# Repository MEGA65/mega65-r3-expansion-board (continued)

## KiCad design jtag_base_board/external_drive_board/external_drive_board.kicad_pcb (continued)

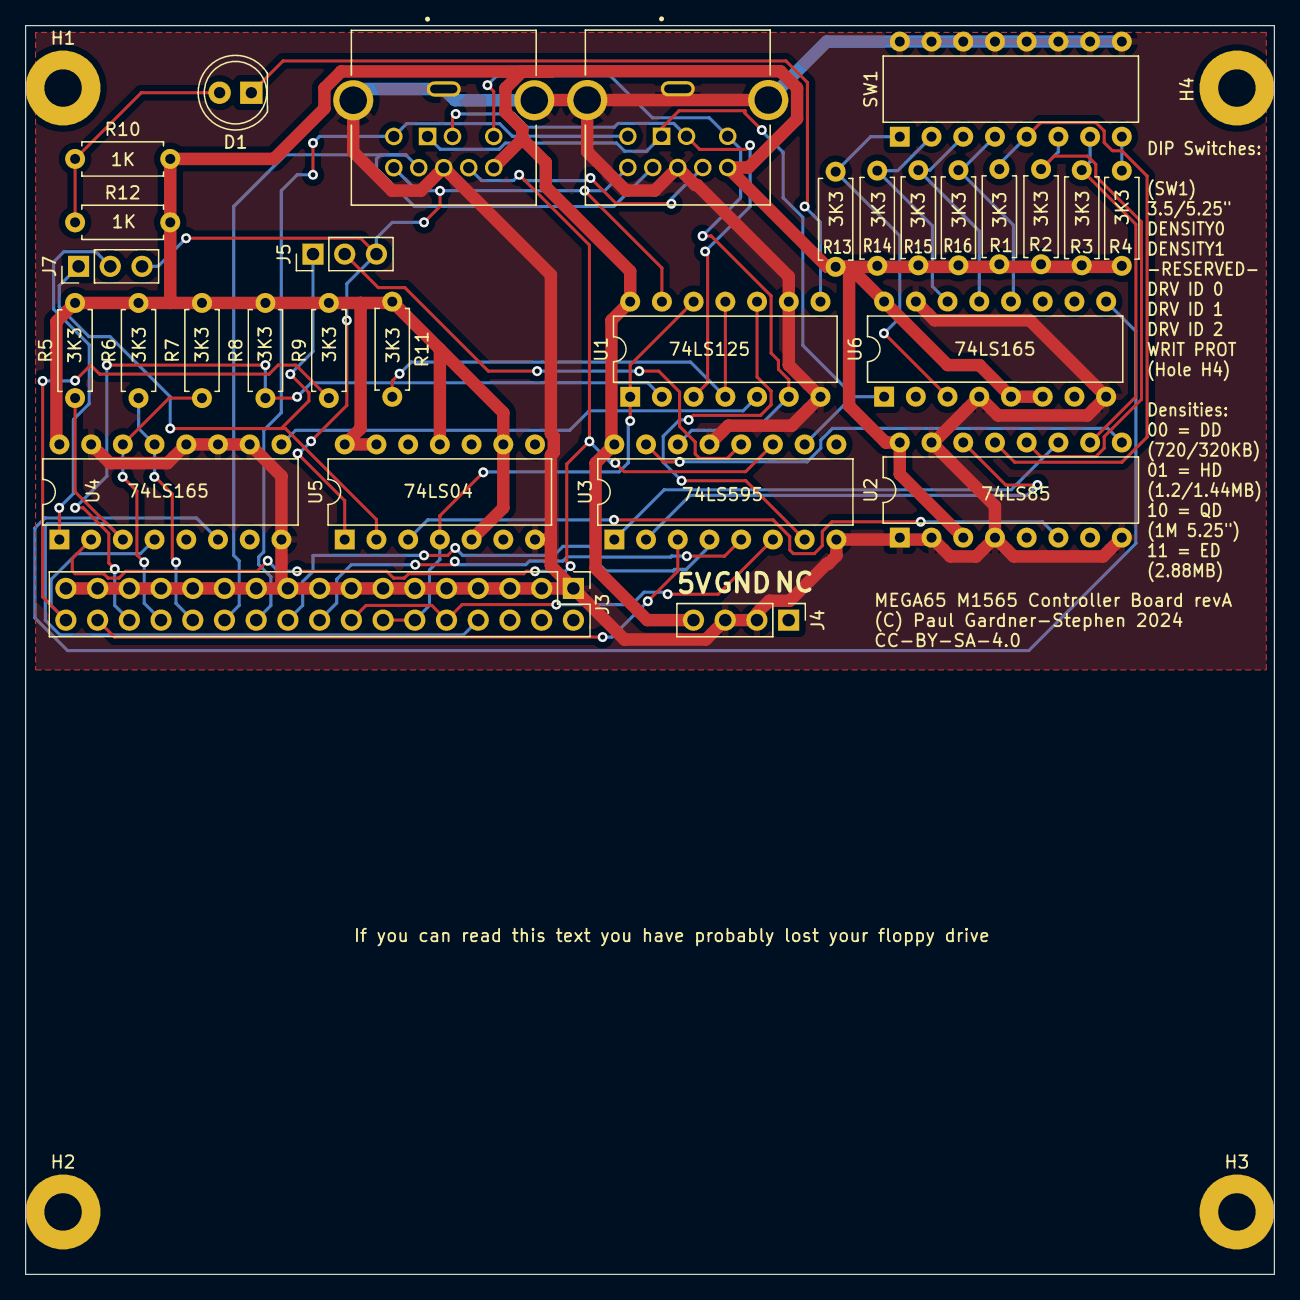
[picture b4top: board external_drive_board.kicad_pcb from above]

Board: 2 copper layers, 100.0 x 100.0 mm, 34 parts (0 on the bottom side), 40 nets.

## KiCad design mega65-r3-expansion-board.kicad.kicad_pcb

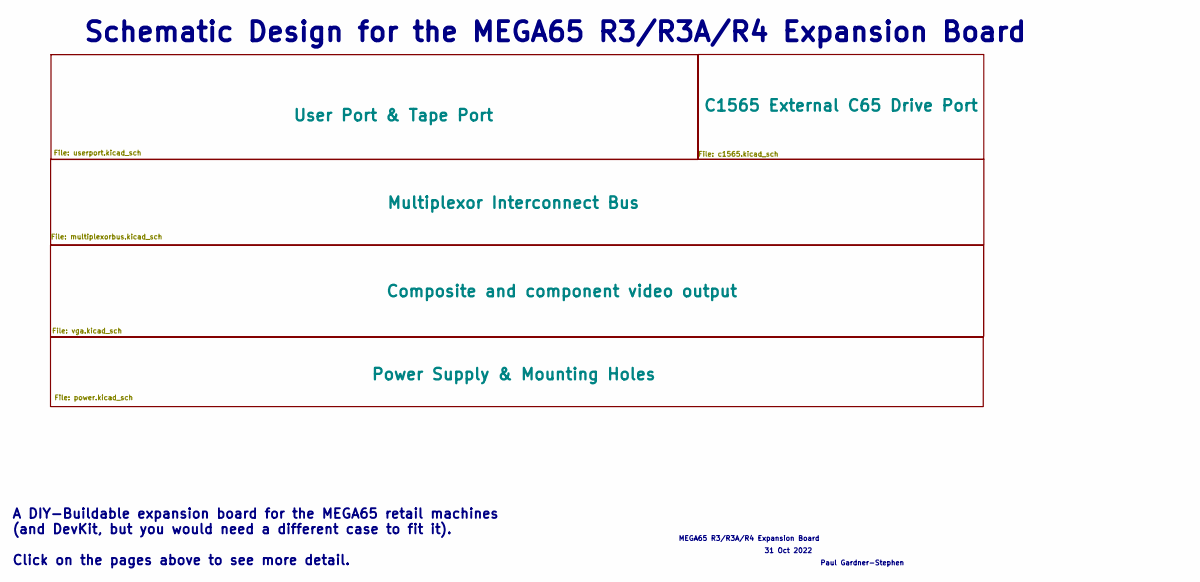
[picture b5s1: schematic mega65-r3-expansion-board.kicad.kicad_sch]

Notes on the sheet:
Paul Gardner-Stephen
A DIY-Buildable expansion board for the MEGA65 retail machines (and DevKit, but you would need a different case to fit it). Click on the pages above to see more detail.
31 Oct 2022
MEGA65 R3/R3A/R4 Expansion Board
Schematic Design for the MEGA65 R3/R3A/R4 Expansion Board

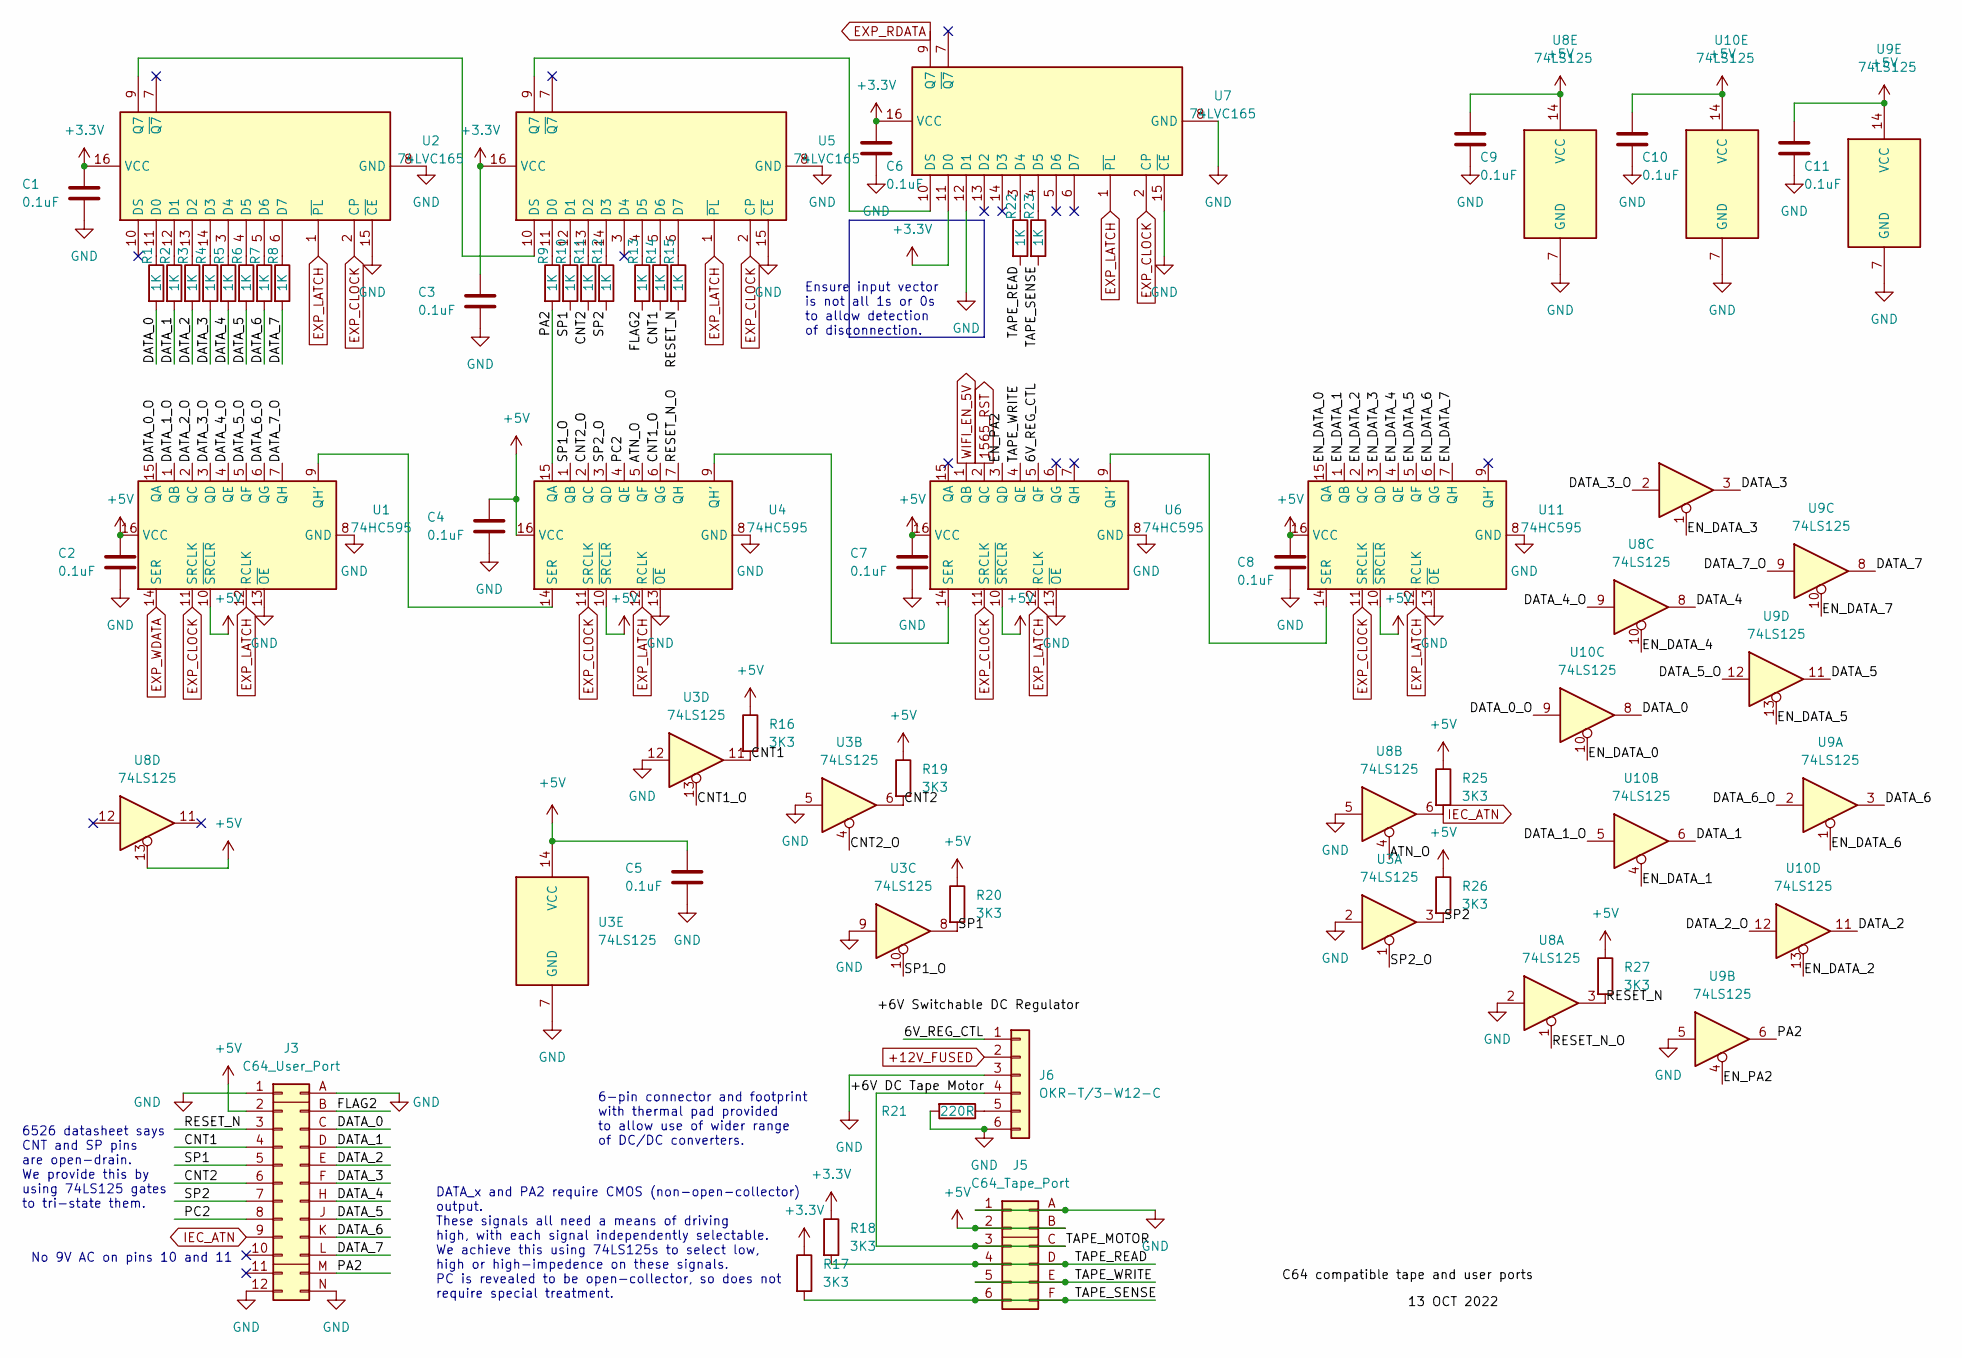
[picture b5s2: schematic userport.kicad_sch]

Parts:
C1, C2, C3, C4, C5, C6, C7, C8, C9, C10, C11: 0.1uF; C_Disc_D5.0mm_W2.5mm_P5.00mm
J3: C64_User_Port; C64-User-Port-Male
J5: C64_Tape_Port; C64-Cassette-Port-Male
J6: OKR-T/3-W12-C; TO-220-FP-5
R1, R2, R3, R4, R5, R6, R7, R8, R9, R10, R11, R12, R13, R14, R15, R22, R23: 1K; Labeled Resistor
R16, R17, R18, R19, R20, R25, R26, R27: 3K3; Labeled Resistor
R21: 220R; Labeled Resistor
U1, U4, U6, U11: 74HC595; DIP-16_LS_Family
U2, U5, U7: 74LVC165; DIP-16_LVC_Family
U3, U8, U9, U10: 74LS125; DIP-14_74LS06

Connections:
1565_RST: U6.2 (QC); also elsewhere on the board
+3V3: C1.1, C3.1, C6.1, R17.1, R18.1, U2.16 (VCC), U5.16 (VCC), U7.11 (D0), U7.16 (VCC); also elsewhere on the board
+5V: C2.1, C4.1, C5.1, C7.1, C8.1, C9.1, C10.1, C11.1, J3.2, J5.2, J5.B, R16.1, R19.1, R20.1, R25.1, R26.1, R27.1, U1.10 (~SRCLR), U1.16 (VCC), U3.14 (VCC), U4.10 (~SRCLR), U4.16 (VCC), U6.10 (~SRCLR), U6.16 (VCC), U8.13, U8.14 (VCC), U9.14 (VCC), U10.14 (VCC), U11.10 (~SRCLR), U11.16 (VCC); also elsewhere on the board
+12V_FUSED: J6.2; also elsewhere on the board
/User Port & Tape Port/6V_REG_CTL: J6.1, U6.5 (QF)
/User Port & Tape Port/ATN_O: U4.5 (QF), U8.4
/User Port & Tape Port/CNT1: J3.4, R14.2, R16.2, U3.11
/User Port & Tape Port/CNT1_O: U3.13, U4.6 (QG)
/User Port & Tape Port/CNT2: J3.6, R11.2, R19.2, U3.6
/User Port & Tape Port/CNT2_O: U3.4, U4.2 (QC)
/User Port & Tape Port/DATA_0: J3.C, R1.2, U10.8
/User Port & Tape Port/DATA_0_O: U1.15 (QA), U10.9
/User Port & Tape Port/DATA_1: J3.D, R2.2, U10.6
/User Port & Tape Port/DATA_1_O: U1.1 (QB), U10.5
/User Port & Tape Port/DATA_2: J3.E, R3.2, U10.11
/User Port & Tape Port/DATA_2_O: U1.2 (QC), U10.12
/User Port & Tape Port/DATA_3: J3.F, R4.2, U10.3
/User Port & Tape Port/DATA_3_O: U1.3 (QD), U10.2
/User Port & Tape Port/DATA_4: J3.H, R5.2, U8.8
/User Port & Tape Port/DATA_4_O: U1.4 (QE), U8.9
/User Port & Tape Port/DATA_5: J3.J, R6.2, U9.11
/User Port & Tape Port/DATA_5_O: U1.5 (QF), U9.12
/User Port & Tape Port/DATA_6: J3.K, R7.2, U9.3
/User Port & Tape Port/DATA_6_O: U1.6 (QG), U9.2
/User Port & Tape Port/DATA_7: J3.L, R8.2, U9.8
/User Port & Tape Port/DATA_7_O: U1.7 (QH), U9.9
/User Port & Tape Port/EN_DATA_0: U10.10, U11.15 (QA)
/User Port & Tape Port/EN_DATA_1: U10.4, U11.1 (QB)
/User Port & Tape Port/EN_DATA_2: U10.13, U11.2 (QC)
/User Port & Tape Port/EN_DATA_3: U10.1, U11.3 (QD)
/User Port & Tape Port/EN_DATA_4: U8.10, U11.4 (QE)
/User Port & Tape Port/EN_DATA_5: U9.13, U11.5 (QF)
/User Port & Tape Port/EN_DATA_6: U9.1, U11.6 (QG)
/User Port & Tape Port/EN_DATA_7: U9.10, U11.7 (QH)
/User Port & Tape Port/EN_PA2: U6.3 (QD), U9.4
/User Port & Tape Port/FLAG2: J3.B, R13.2
/User Port & Tape Port/PA2: J3.M, R9.2, U4.15 (QA), U9.6
/User Port & Tape Port/PC2: J3.8, U4.4 (QE)
/User Port & Tape Port/RESET_N: J3.3, R15.2, R27.2, U8.3
/User Port & Tape Port/RESET_N_O: U4.7 (QH), U8.1
/User Port & Tape Port/SP1: J3.5, R10.2, R20.2, U3.8
/User Port & Tape Port/SP1_O: U3.10, U4.1 (QB)
/User Port & Tape Port/SP2: J3.7, R12.2, R26.2, U3.3
/User Port & Tape Port/SP2_O: U3.1, U4.3 (QD)
/User Port & Tape Port/TAPE_MOTOR: J5.3, J5.C, J6.4
/User Port & Tape Port/TAPE_READ: J5.4, J5.D, R18.2, R22.2
/User Port & Tape Port/TAPE_SENSE: J5.6, J5.F, R17.2, R23.2
/User Port & Tape Port/TAPE_WRITE: J5.5, J5.E, U6.4 (QE)
EXP_CLOCK: U1.11 (SRCLK), U2.2 (CP), U4.11 (SRCLK), U5.2 (CP), U6.11 (SRCLK), U7.2 (CP), U11.11 (SRCLK); also elsewhere on the board
EXP_LATCH: U1.12 (RCLK), U2.1 (~PL), U4.12 (RCLK), U5.1 (~PL), U6.12 (RCLK), U7.1 (~PL), U11.12 (RCLK); also elsewhere on the board
EXP_RDATA: U7.9 (Q7); also elsewhere on the board
EXP_WDATA: U1.14 (SER); also elsewhere on the board
GND: C1.2, C2.2, C3.2, C4.2, C5.2, C6.2, C7.2, C8.2, C9.2, C10.2, C11.2, J3.1, J3.12, J3.A, J3.N, J5.1, J5.A, J6.3, J6.6, R21.2, U1.8 (GND), U1.13 (~OE), U2.8 (GND), U2.15 (~CE), U3.2, U3.5, U3.7 (GND), U3.9, U3.12, U4.8 (GND), U4.13 (~OE), U5.8 (GND), U5.15 (~CE), U6.8 (GND), U6.13 (~OE), U7.8 (GND), U7.12 (D1), U7.15 (~CE), U8.2, U8.5, U8.7 (GND), U9.5, U9.7 (GND), U10.7 (GND), U11.8 (GND), U11.13 (~OE); also elsewhere on the board
IEC_ATN: J3.9, R25.2, U8.6
unnamed: J6.5, R21.1
unnamed: U1.9 (QH'), U4.14 (SER)
unnamed: R1.1, U2.11 (D0)
unnamed: R2.1, U2.12 (D1)
unnamed: R3.1, U2.13 (D2)
unnamed: R4.1, U2.14 (D3)
unnamed: R5.1, U2.3 (D4)
unnamed: R6.1, U2.4 (D5)
unnamed: R7.1, U2.5 (D6)
unnamed: R8.1, U2.6 (D7)
unnamed: U2.9 (Q7), U5.10 (DS)
unnamed: U4.9 (QH'), U6.14 (SER)
unnamed: R9.1, U5.11 (D0)
unnamed: R10.1, U5.12 (D1)
unnamed: R11.1, U5.13 (D2)
unnamed: R12.1, U5.14 (D3)
unnamed: R13.1, U5.4 (D5)
unnamed: R14.1, U5.5 (D6)
unnamed: R15.1, U5.6 (D7)
unnamed: U5.9 (Q7), U7.10 (DS)
unnamed: R22.1, U7.3 (D4)
unnamed: R23.1, U7.4 (D5)
unnamed: U6.9 (QH'), U11.14 (SER)
WIFI_EN_5V: U6.1 (QB); also elsewhere on the board

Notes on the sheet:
No 9V AC on pins 10 and 11
6526 datasheet says CNT and SP pins are open-drain. We provide this by using 74LS125 gates to tri-state them.
Ensure input vector is not all 1s or 0s to allow detection of disconnection.
6-pin connector and footprint with thermal pad provided to allow use of wider range of DC/DC converters.
DATA_x and PA2 require CMOS (non-open-collector) output. These signals all need a means of driving high, with each signal independently selectable. We achieve this using 74LS125s to select low, high or high-impedence on these signals. PC is revealed to be open-collector, so does not require special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

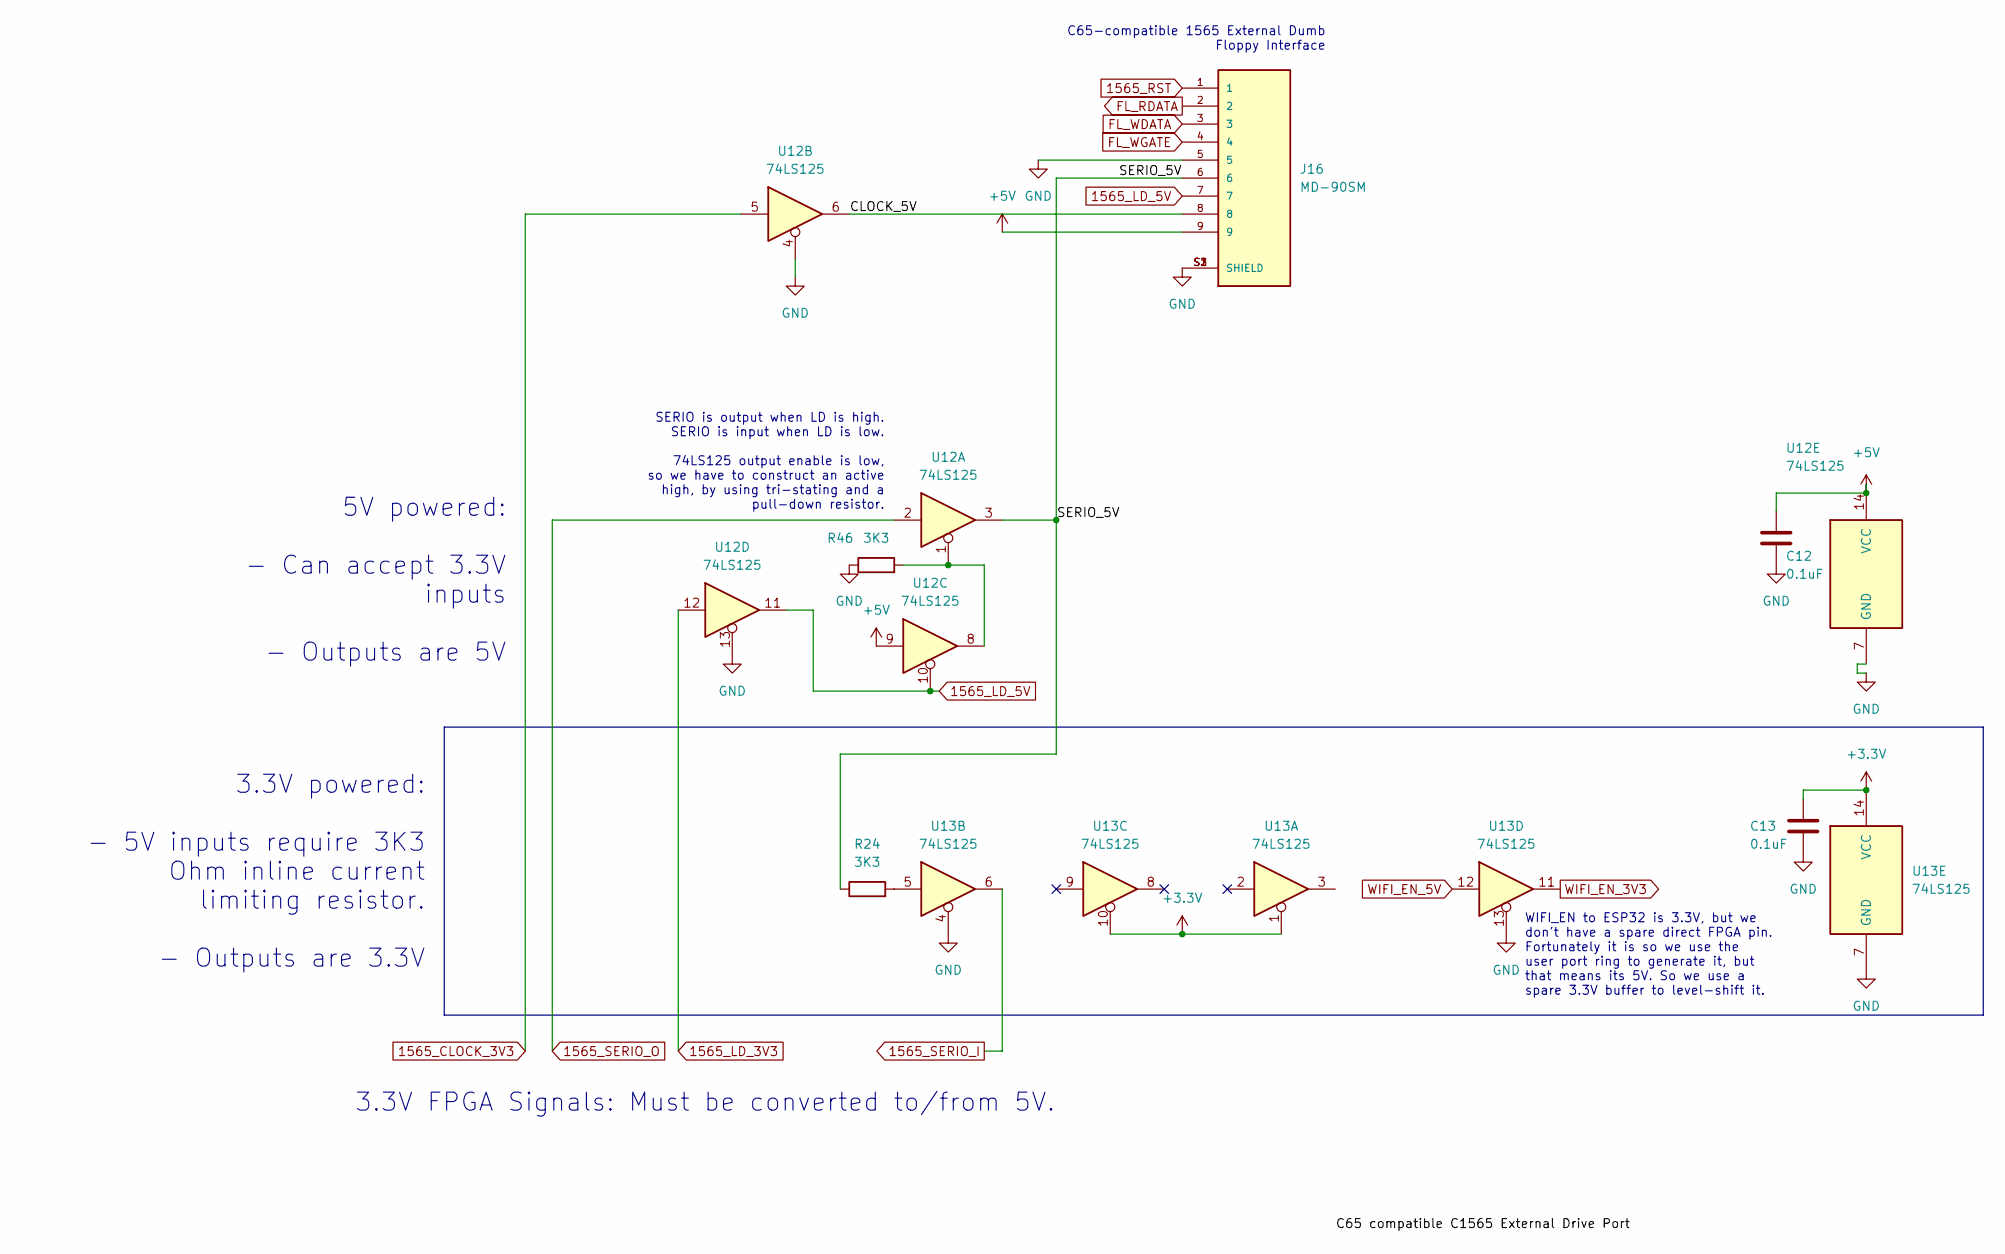
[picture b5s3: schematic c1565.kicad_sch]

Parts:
C12, C13: 0.1uF; C_Disc_D5.0mm_W2.5mm_P5.00mm
J16: MD-90SM; CUI_MD-90SM; PARTREV 02/18/2022
R24, R46: 3K3; Labeled Resistor
U12: 74LS125; DIP-14_W7.62mm
U13: 74LS125; DIP-14_74LS06

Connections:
1565_CLOCK_3V3: U12.5; also elsewhere on the board
1565_LD_3V3: U12.12; also elsewhere on the board
1565_LD_5V: J16.7, U12.10, U12.11
1565_RST: J16.1; also elsewhere on the board
1565_SERIO_I: U13.6; also elsewhere on the board
1565_SERIO_O: U12.2; also elsewhere on the board
+3V3: C13.1, U13.1, U13.10, U13.14 (VCC); also elsewhere on the board
+5V: C12.1, J16.9, U12.9, U12.14 (VCC); also elsewhere on the board
/C1565 External C65 Drive Port/CLOCK_5V: J16.8, U12.6
/C1565 External C65 Drive Port/SERIO_5V: J16.6, R24.1, U12.3
FL_RDATA: J16.2; also elsewhere on the board
FL_WDATA: J16.3; also elsewhere on the board
FL_WGATE: J16.4; also elsewhere on the board
GND: C12.2, C13.2, J16.5, J16.S1 (SHIELD), J16.S2 (SHIELD), J16.S3 (SHIELD), R46.1, U12.4, U12.7 (GND), U12.13, U13.4, U13.7 (GND), U13.13; also elsewhere on the board
unnamed: R24.2, U13.5
unnamed: R46.2, U12.1, U12.8
WIFI_EN_3V3: U13.11; also elsewhere on the board
WIFI_EN_5V: U13.12; also elsewhere on the board

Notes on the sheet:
5V powered: - Can accept 3.3V inputs - Outputs are 5V
3.3V powered: - 5V inputs require 3K3 Ohm inline current limiting resistor. - Outputs are 3.3V
C65-compatible 1565 External Dumb Floppy Interface
SERIO is output when LD is high. SERIO is input when LD is low. 74LS125 output enable is low, so we have to construct an active high, by using tri-stating and a pull-down resistor.
3.3V FPGA Signals: Must be converted to/from 5V.
WIFI_EN to ESP32 is 3.3V, but we don't have a spare direct FPGA pin. Fortunately it is so we use the user port ring to generate it, but that means its 5V. So we use a spare 3.3V buffer to level-shift it.

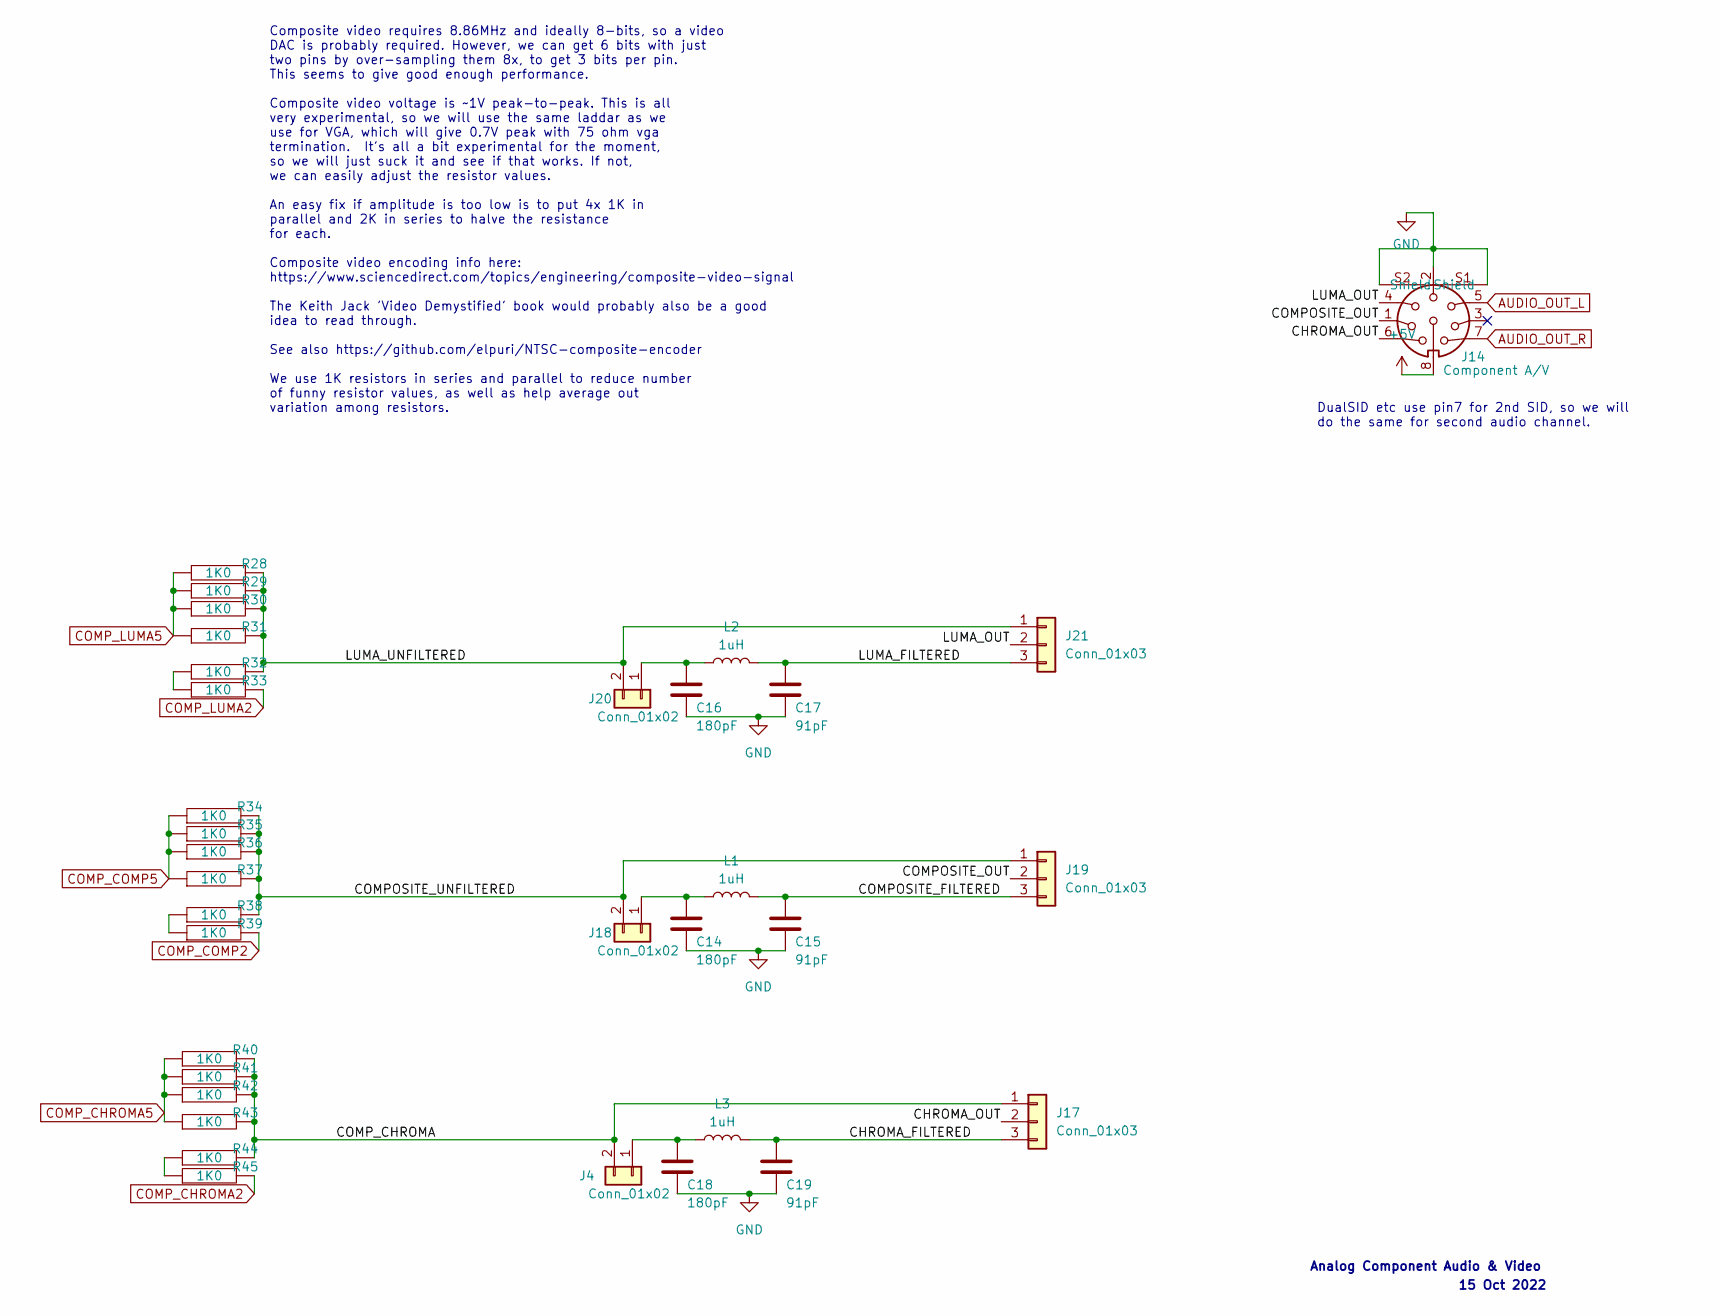
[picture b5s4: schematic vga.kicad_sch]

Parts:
C14, C16, C18: 180pF; C_Disc_D5.0mm_W2.5mm_P5.00mm
C15, C17, C19: 91pF; C_Disc_D5.0mm_W2.5mm_P5.00mm
J4, J18, J20: Conn_01x02; PinSocket_1x02_P2.54mm_Vertical
J14: Component A/V; CUI_SDF-80J
J17, J19, J21: Conn_01x03; PinSocket_1x03_P2.54mm_Vertical
L1, L2, L3: 1uH; L_Axial_L6.6mm_D2.7mm_P2.54mm_Vertical_Vishay_IM-2
R28, R29, R30, R31, R32, R33, R34, R35, R36, R37, R38, R39, R40, R41, R42, R43, R44, R45: 1K0; Labeled Resistor

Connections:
+5V: J14.8; also elsewhere on the board
/Composite and component video output/CHROMA_FILTERED: C19.1, J17.3, L3.2
/Composite and component video output/CHROMA_OUT: J14.6, J17.2
/Composite and component video output/COMPOSITE_FILTERED: C15.1, J19.3, L1.2
/Composite and component video output/COMPOSITE_OUT: J14.1, J19.2
/Composite and component video output/COMPOSITE_UNFILTERED: J18.2, J19.1, R34.2, R35.2, R36.2, R37.2, R38.2
/Composite and component video output/COMP_CHROMA: J4.2, J17.1, R40.2, R41.2, R42.2, R43.2, R44.2
/Composite and component video output/LUMA_FILTERED: C17.1, J21.3, L2.2
/Composite and component video output/LUMA_OUT: J14.4, J21.2
/Composite and component video output/LUMA_UNFILTERED: J20.2, J21.1, R28.2, R29.2, R30.2, R31.2, R32.2
AUDIO_OUT_L: J14.5; also elsewhere on the board
AUDIO_OUT_R: J14.3; also elsewhere on the board
COMP_CHROMA2: R45.2; also elsewhere on the board
COMP_CHROMA5: R40.1, R41.1, R42.1, R43.1; also elsewhere on the board
COMP_COMP2: R39.2; also elsewhere on the board
COMP_COMP5: R34.1, R35.1, R36.1, R37.1; also elsewhere on the board
COMP_LUMA2: R33.2; also elsewhere on the board
COMP_LUMA5: R28.1, R29.1, R30.1, R31.1; also elsewhere on the board
GND: C14.2, C15.2, C16.2, C17.2, C18.2, C19.2, J14.2, J14.S1 (Shield), J14.S2 (Shield); also elsewhere on the board
unnamed: C18.1, J4.1, L3.1
unnamed: C14.1, J18.1, L1.1
unnamed: C16.1, J20.1, L2.1
unnamed: R32.1, R33.1
unnamed: R38.1, R39.1
unnamed: R44.1, R45.1

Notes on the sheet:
15 Oct 2022
Composite video requires 8.86MHz and ideally 8-bits, so a video DAC is probably required. However, we can get 6 bits with just two pins by over-sampling them 8x, to get 3 bits per pin. This seems to give good enough performance. Composite video voltage is ~1V peak-to-peak. This is all very experime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
DualSID etc use pin7 for 2nd SID, so we will do the same for second audio channel.
Analog Component Audio & Video

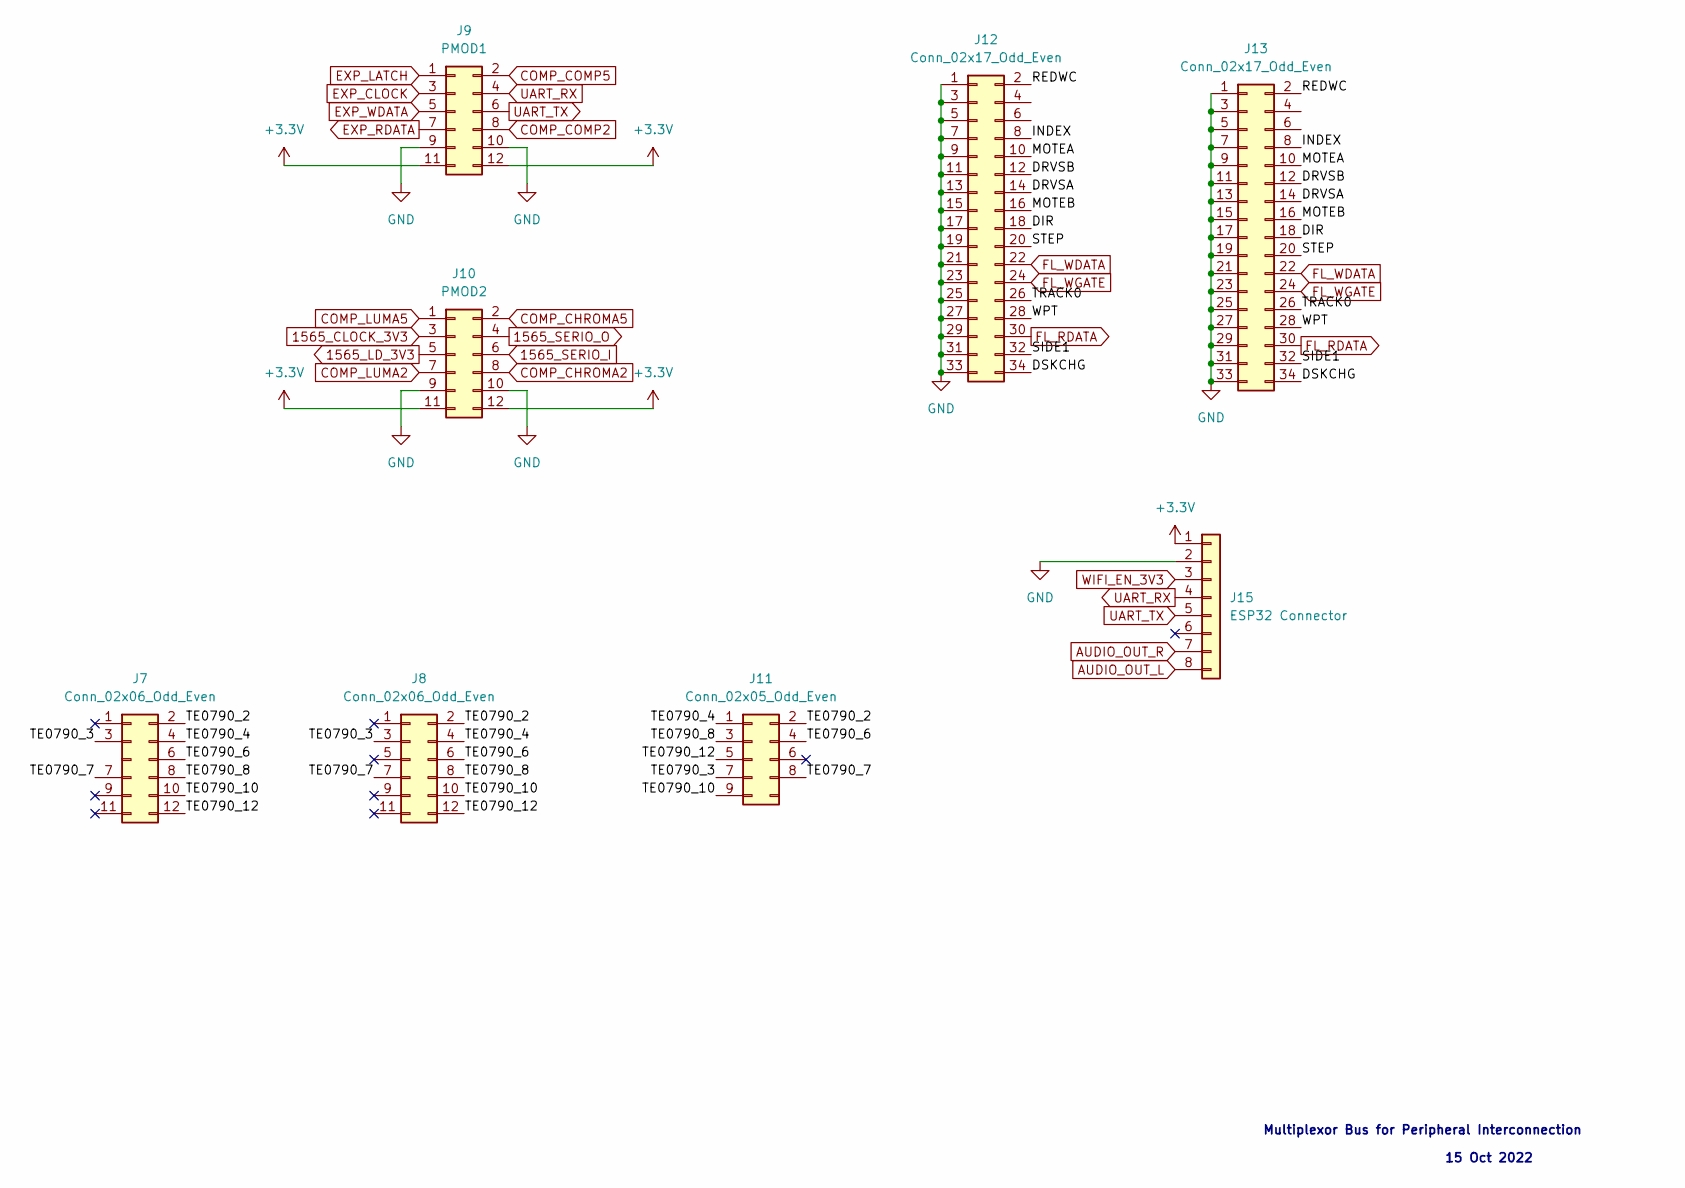
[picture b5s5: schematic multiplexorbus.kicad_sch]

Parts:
J7, J8: Conn_02x06_Odd_Even; PinHeader_2x06_P2.54mm_Vertical
J9: PMOD1; PinHeader_2x06_P2.54mm_Vertical
J10: PMOD2; PinHeader_2x06_P2.54mm_Vertical
J11: Conn_02x05_Odd_Even; PinHeader_2x05_P2.54mm_Vertical
J12, J13: Conn_02x17_Odd_Even; PinHeader_2x17_P2.54mm_Vertical
J15: ESP32 Connector; PinHeader_1x08_P2.54mm_Vertical

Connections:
1565_CLOCK_3V3: J10.3; also elsewhere on the board
1565_LD_3V3: J10.5; also elsewhere on the board
1565_SERIO_I: J10.6; also elsewhere on the board
1565_SERIO_O: J10.4; also elsewhere on the board
+3V3: J9.11, J9.12, J10.11, J10.12, J15.1; also elsewhere on the board
/Multiplexor Interconnect Bus/DIR: J12.18, J13.18
/Multiplexor Interconnect Bus/DRVSA: J12.14, J13.14
/Multiplexor Interconnect Bus/DRVSB: J12.12, J13.12
/Multiplexor Interconnect Bus/DSKCHG: J12.34, J13.34
/Multiplexor Interconnect Bus/INDEX: J12.8, J13.8
/Multiplexor Interconnect Bus/MOTEA: J12.10, J13.10
/Multiplexor Interconnect Bus/MOTEB: J12.16, J13.16
/Multiplexor Interconnect Bus/REDWC: J12.2, J13.2
/Multiplexor Interconnect Bus/SIDE1: J12.32, J13.32
/Multiplexor Interconnect Bus/STEP: J12.20, J13.20
/Multiplexor Interconnect Bus/TE0790_2: J7.2, J8.2, J11.2
/Multiplexor Interconnect Bus/TE0790_3: J7.3, J8.3, J11.7
/Multiplexor Interconnect Bus/TE0790_4: J7.4, J8.4, J11.1
/Multiplexor Interconnect Bus/TE0790_6: J7.6, J8.6, J11.4
/Multiplexor Interconnect Bus/TE0790_7: J7.7, J8.7, J11.8
/Multiplexor Interconnect Bus/TE0790_8: J7.8, J8.8, J11.3
/Multiplexor Interconnect Bus/TE0790_10: J7.10, J8.10, J11.9
/Multiplexor Interconnect Bus/TE0790_12: J7.12, J8.12, J11.5
/Multiplexor Interconnect Bus/TRACK0: J12.26, J13.26
/Multiplexor Interconnect Bus/WPT: J12.28, J13.28
AUDIO_OUT_L: J15.8; also elsewhere on the board
AUDIO_OUT_R: J15.7; also elsewhere on the board
COMP_CHROMA2: J10.8; also elsewhere on the board
COMP_CHROMA5: J10.2; also elsewhere on the board
COMP_COMP2: J9.8; also elsewhere on the board
COMP_COMP5: J9.2; also elsewhere on the board
COMP_LUMA2: J10.7; also elsewhere on the board
COMP_LUMA5: J10.1; also elsewhere on the board
EXP_CLOCK: J9.3; also elsewhere on the board
EXP_LATCH: J9.1; also elsewhere on the board
EXP_RDATA: J9.7; also elsewhere on the board
EXP_WDATA: J9.5; also elsewhere on the board
FL_RDATA: J12.30, J13.30; also elsewhere on the board
FL_WDATA: J12.22, J13.22; also elsewhere on the board
FL_WGATE: J12.24, J13.24; also elsewhere on the board
GND: J9.9, J9.10, J10.9, J10.10, J12.1, J12.3, J12.5, J12.7, J12.9, J12.11, J12.13, J12.15, J12.17, J12.19, J12.21, J12.23, J12.25, J12.27, J12.29, J12.31, J12.33, J13.1, J13.3, J13.5, J13.7, J13.9, J13.11, J13.13, J13.15, J13.17, J13.19, J13.21, J13.23, J13.25, J13.27, J13.29, J13.31, J13.33, J15.2; also elsewhere on the board
UART_RX: J9.4, J15.4
UART_TX: J9.6, J15.5
WIFI_EN_3V3: J15.3; also elsewhere on the board

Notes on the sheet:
Multiplexor Bus for Peripheral Interconnection
15 Oct 2022

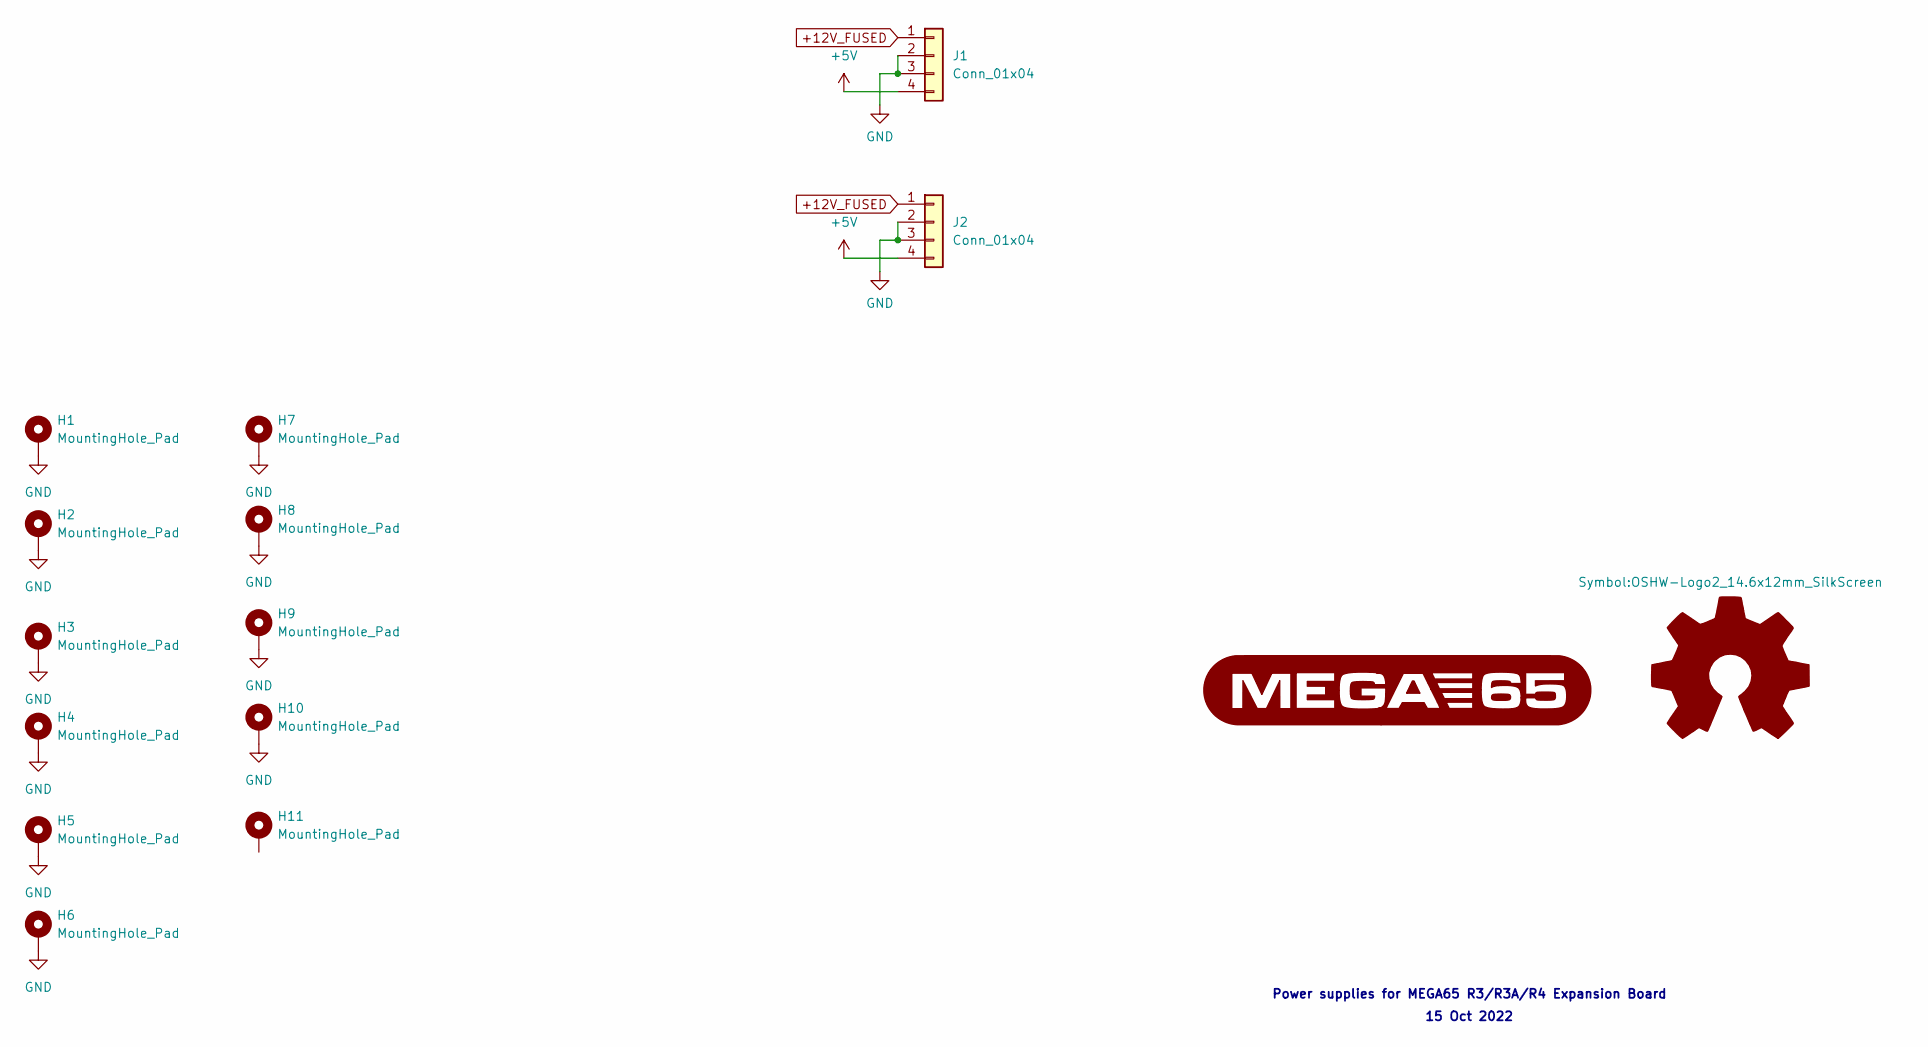
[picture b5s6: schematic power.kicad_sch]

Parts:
H1, H2, H3, H4, H5, H6, H7, H8, H9, H10, H11: MountingHole_Pad; MountingHole_3.2mm_M3_DIN965_Pad
J1, J2: Conn_01x04; FloppyPower
LOGO1: Logo_Open_Hardware_Large; OSHW-Logo2_14.6x12mm_SilkScreen

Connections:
+5V: J1.4, J2.4; also elsewhere on the board
+12V_FUSED: J1.1, J2.1; also elsewhere on the board
GND: H1.1, H2.1, H3.1, H4.1, H5.1, H6.1, H7.1, H8.1, H9.1, H10.1, J1.2, J1.3, J2.2, J2.3; also elsewhere on the board

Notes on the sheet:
Power supplies for MEGA65 R3/R3A/R4 Expansion Board
15 Oct 2022
